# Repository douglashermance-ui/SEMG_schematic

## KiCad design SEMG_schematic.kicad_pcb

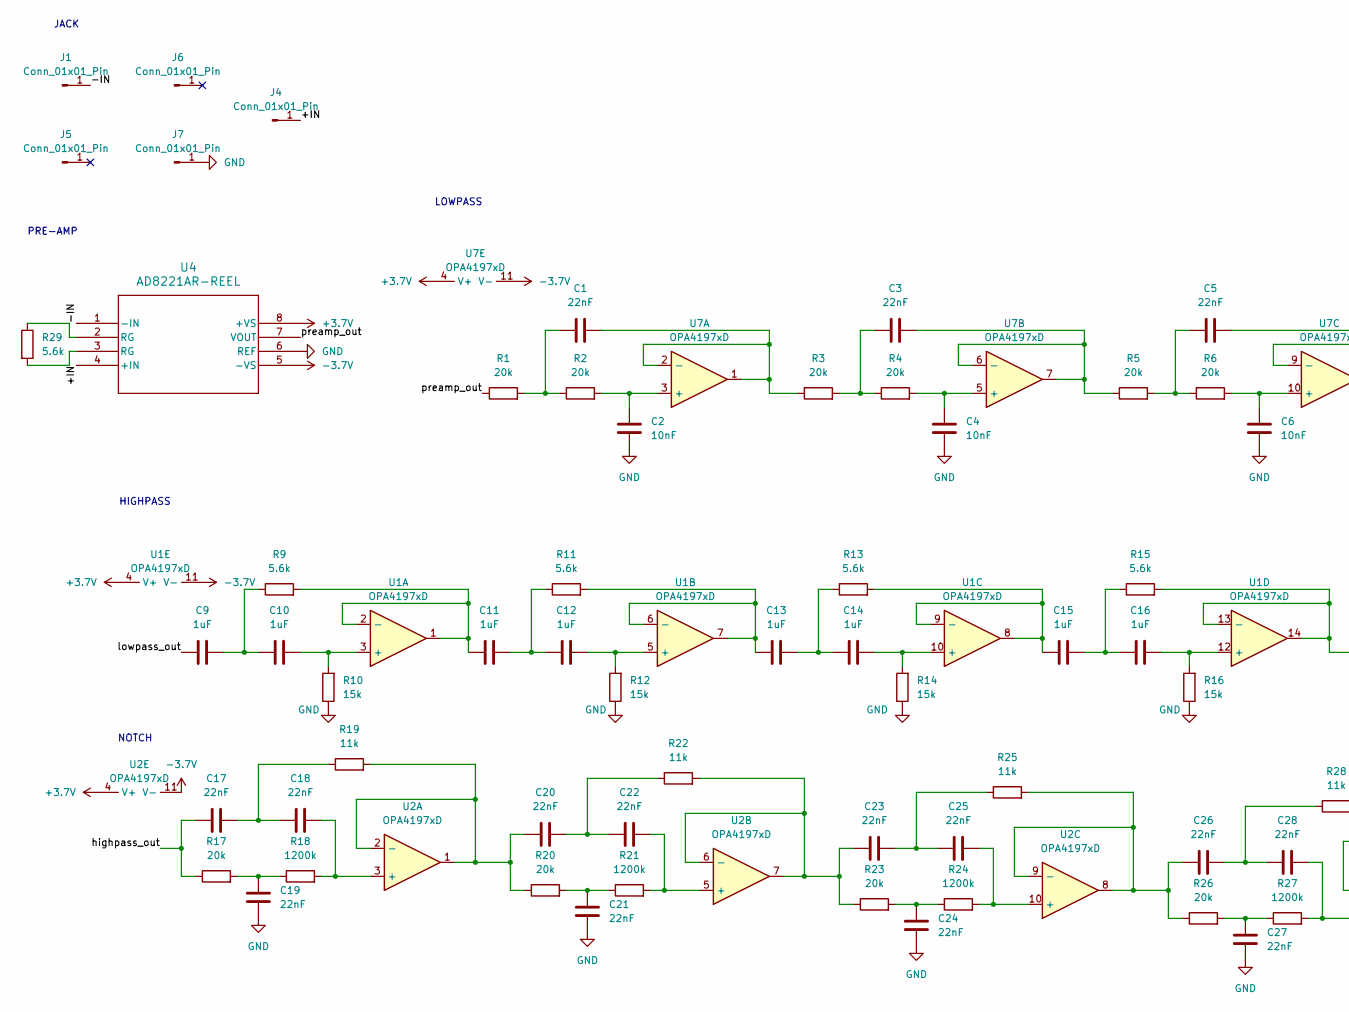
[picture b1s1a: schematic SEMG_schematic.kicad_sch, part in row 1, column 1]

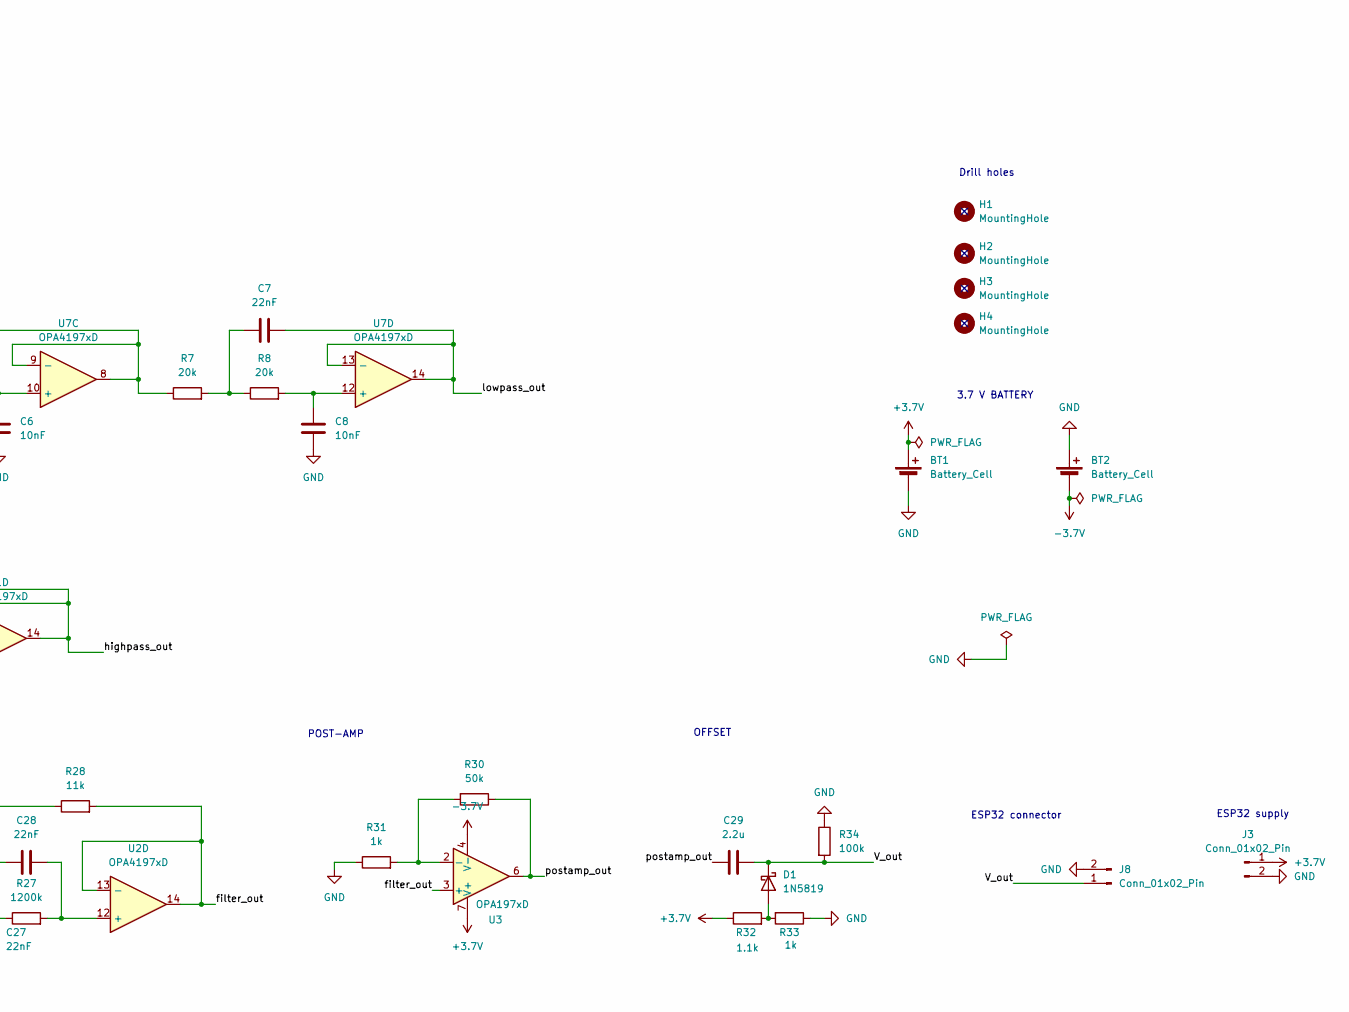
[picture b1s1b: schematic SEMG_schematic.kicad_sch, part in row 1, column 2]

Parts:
BT1, BT2: Battery_Cell; PinHeader_1x02_P2.54mm_Vertical
C1, C3, C5, C7, C17, C18, C19, C20, C21, C22, C23, C24, C25, C26, C27, C28: 22nF; C_Disc_D5.0mm_W2.5mm_P5.00mm
C2, C4, C6, C8: 10nF; C_Disc_D5.0mm_W2.5mm_P5.00mm
C9, C10, C11, C12, C13, C14, C15, C16: 1uF; C_Disc_D5.0mm_W2.5mm_P5.00mm
C29: 2.2u; C_Disc_D5.0mm_W2.5mm_P5.00mm
D1: 1N5819; D_DO-41_SOD81_P10.16mm_Horizontal
H1, H2, H3, H4: MountingHole; MountingHole_3.2mm_M3
J1, J4, J5, J6, J7: Conn_01x01_Pin; PinSocket_1x01_P2.54mm_Vertical
J3, J8: Conn_01x02_Pin; PinHeader_1x02_P2.54mm_Vertical
R1, R2, R3, R4, R5, R6, R7, R8, R17, R20, R23, R26: 20k; R_Axial_DIN0207_L6.3mm_D2.5mm_P10.16mm_Horizontal
R9, R11, R13, R15, R29: 5.6k; R_Axial_DIN0207_L6.3mm_D2.5mm_P10.16mm_Horizontal
R10, R12, R14, R16: 15k; R_Axial_DIN0207_L6.3mm_D2.5mm_P10.16mm_Horizontal
R18, R21, R24, R27: 1200k; R_Axial_DIN0207_L6.3mm_D2.5mm_P10.16mm_Horizontal
R19, R22, R25, R28: 11k; R_Axial_DIN0207_L6.3mm_D2.5mm_P10.16mm_Horizontal
R30: 50k; R_Axial_DIN0207_L6.3mm_D2.5mm_P10.16mm_Horizontal
R31, R33: 1k; R_Axial_DIN0207_L6.3mm_D2.5mm_P10.16mm_Horizontal
R32: 1.1k; R_Axial_DIN0207_L6.3mm_D2.5mm_P10.16mm_Horizontal
R34: 100k; R_Axial_DIN0207_L6.3mm_D2.5mm_P10.16mm_Horizontal
U1, U2, U7: OPA4197xD; SOIC-14_3.9x8.7mm_P1.27mm
U3: OPA197xD; SOIC-8_3.9x4.9mm_P1.27mm
U4: AD8221AR-REEL; MSOP-8_3x3mm_P0.65mm

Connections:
+3.7V: BT1.1 (+), J3.1, R32.1, U1.4 (V+), U2.4 (V+), U3.7 (V+), U4.8 (+VS), U7.4 (V+)
-3.7V: BT2.2 (-), U1.11 (V-), U2.11 (V-), U3.4 (V-), U4.5 (-VS), U7.11 (V-)
/+IN: J4.1, U4.4 (+IN)
/-IN: J1.1, U4.1 (-IN)
/V_out: C29.2, D1.1 (K), J8.1, R34.2
/filter_out: R28.2, U2.13 (-), U2.14, U3.3 (+)
/highpass_out: C17.1, R15.2, R17.1, U1.13 (-), U1.14
/lowpass_out: C7.2, C9.1, U7.13 (-), U7.14
/postamp_out: C29.1, R30.1, U3.6
/preamp_out: R1.1, U4.7 (VOUT)
GND: BT1.2 (-), BT2.1 (+), C2.2, C4.2, C6.2, C8.2, C19.1, C21.1, C24.1, C27.1, J3.2, J7.1, J8.2, R10.1, R12.1, R14.1, R16.1, R31.1, R33.1, R34.1, U4.6 (REF)
unnamed: C1.1, R1.2, R2.1
unnamed: C3.1, R3.2, R4.1
unnamed: C5.1, R5.2, R6.1
unnamed: C7.1, R7.2, R8.1
unnamed: C9.2, C10.1, R9.1
unnamed: C11.2, C12.1, R11.1
unnamed: C13.2, C14.1, R13.1
unnamed: C15.2, C16.1, R15.1
unnamed: C17.2, C18.1, R19.1
unnamed: C19.2, R17.2, R18.1
unnamed: C20.2, C22.1, R22.1
unnamed: C21.2, R20.2, R21.1
unnamed: C23.2, C25.1, R25.1
unnamed: C24.2, R23.2, R24.1
unnamed: C26.2, C28.1, R28.1
unnamed: C27.2, R26.2, R27.1
unnamed: D1.2 (A), R32.2, R33.2
unnamed: R29.1, U4.2 (RG)
unnamed: R29.2, U4.3 (RG)
unnamed: C10.2, R10.2, U1.3 (+)
unnamed: C11.1, R9.2, U1.1, U1.2 (-)
unnamed: C12.2, R12.2, U1.5 (+)
unnamed: C13.1, R11.2, U1.6 (-), U1.7
unnamed: C14.2, R14.2, U1.10 (+)
unnamed: C15.1, R13.2, U1.8, U1.9 (-)
unnamed: C16.2, R16.2, U1.12 (+)
unnamed: C18.2, R18.2, U2.3 (+)
unnamed: C20.1, R19.2, R20.1, U2.1, U2.2 (-)
unnamed: C22.2, R21.2, U2.5 (+)
unnamed: C23.1, R22.2, R23.1, U2.6 (-), U2.7
unnamed: C25.2, R24.2, U2.10 (+)
unnamed: C26.1, R25.2, R26.1, U2.8, U2.9 (-)
unnamed: C28.2, R27.2, U2.12 (+)
unnamed: R30.2, R31.2, U3.2 (-)
unnamed: C2.1, R2.2, U7.3 (+)
unnamed: C1.2, R3.1, U7.1, U7.2 (-)
unnamed: C4.1, R4.2, U7.5 (+)
unnamed: C3.2, R5.1, U7.6 (-), U7.7
unnamed: C6.1, R6.2, U7.10 (+)
unnamed: C5.2, R7.1, U7.8, U7.9 (-)
unnamed: C8.1, R8.2, U7.12 (+)

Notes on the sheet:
OFFSET
HIGHPASS
NOTCH
ESP32 connector
Drill holes
LOWPASS
ESP32 supply
PRE-AMP
POST-AMP
JACK
3.7 V BATTERY

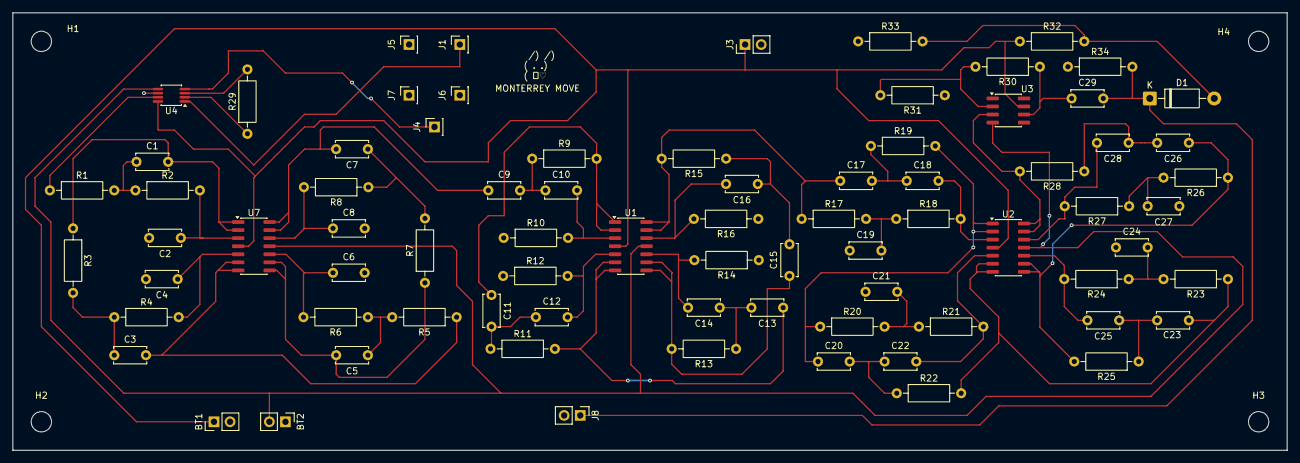
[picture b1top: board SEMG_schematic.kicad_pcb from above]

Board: 2 copper layers, 201.0 x 69.0 mm, 82 parts (0 on the bottom side), 52 nets.
